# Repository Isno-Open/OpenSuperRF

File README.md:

# OpenSuperRF: the ISNO Super radio board, open

*(Version française : [README.fr.md](README.fr.md))*

**OpenSuperRF** is the open design of the **ISNO Super**: a sub-GHz radio board built around an
ESP32-S3, made to cleanly run open radio firmwares such as
[OpenProfalux](https://github.com/Isno-Open/OpenProfalux) (Profalux 868 MHz shutters in Home
Assistant, no gateway).

This is the **v1.0 (EVT)**, the version that was manufactured, assembled and measured. It is
published here as open hardware. The board sold as a pre-order is the **v1.1**, a refinement (see
[v1.0 open, v1.1 sold](#v10-open-v11-sold)).

> ⚠️ **Open points (v1.0 EVT).** This prototype has known open points, including a **J2 mikroBUS pinout that is destructive with a straight IDC cable**. Read [`KNOWN_ISSUES.md`](KNOWN_ISSUES.md) before building.

## What it is

- **ESP32-S3** over USB-C, powered by a 3.3 V LDO.
- **Two CC1101 radios**, **433 MHz and 868 MHz**, driven over SPI.
- On the v1.0, the two radios are combined onto a **single SMA** through an **LC diplexer**.
- **Qwiic** (I2C) and **mikroBUS** (2x8) for expansion.
- **BOOT** and **RESET** buttons, status LED.
- 4 layers, 67 x 55 mm. Board marking: `ISNO Super IoT HW REV 1.0`.

## Firmwares

The Super is not tied to one firmware, it is a board **for radio firmwares**. It notably runs:

- **[OpenProfalux](https://github.com/Isno-Open/OpenProfalux)** : Profalux 868 MHz shutters in Home
  Assistant, no gateway.
- **[OpenRFTest](https://github.com/Isno-Open/OpenRFTest)** : radio test firmware (TX/RX).

## RF measurements (v1.0, tinySA)

The v1.0 was measured: single, clean carriers, low noise floor, no spurious emissions over the
observed window.

## Schematic and pinout

mikroBUS (left column): AN 8, RST 40, CS 34, SCK 36, MISO 37, MOSI 35, 3.3 V, GND.
mikroBUS (right column): PWM 38, INT 39, RX 18, TX 17, SCL 13, SDA 12, 5 V, GND.
Qwiic: GND, 3.3 V, SDA 12, SCL 13.

The full schematic is in [`docs/isno-super-v1.0-schematic.pdf`](docs/isno-super-v1.0-schematic.pdf).

## Enclosure

A 3D-printable enclosure is provided in [`enclosures/`](enclosures/) (`boitier_super.stl`). The board
also fits DIN-rail and IP65 enclosures.

## Accessories

Open here as well (produced, unchanged since). KiCad sources in [`hardware/accessories/`](hardware/accessories/).

- **mikroBUS riser**: raises and offsets the mikroBUS socket.
- **mikroBUS adapter**.

## v1.0 open, v1.1 sold

To be clear, and honest:

- **v1.0** (here, open): the two radios combined onto a **single SMA** through an **LC diplexer**. This
  is the tested and measured version, published as open hardware to study, build and modify.
- **v1.1** (sold as a [pre-order](https://www.isno.fr/boutique/isno-super)): same radio chain
  (ESP32-S3 + dual CC1101), but the diplexer is removed in favour of **two dedicated antenna
  connectors** (one per band). It is the refined, ready-to-use and supported evolution.

DIY therefore stays fully possible and free; the v1.1 is the "ready and reliable" option for those who
would rather not build it.

## Repository contents

- `hardware/super/` : KiCad source of the Super **v1.0** (schematic + PCB).
- `hardware/accessories/` : KiCad source of the accessories (mikroBUS riser, adapter).
- `hardware/OpenProfalux.pretty/`, `hardware/lib/` : custom footprints and symbols needed to open the
  project in KiCad. The `.pretty` library keeps its historical name (the board started under the
  OpenProfalux project); it is just the footprint library.
- `fab/` : the manufactured EVT outputs (Gerbers, BOM, CPL, 3D render, EMC and thermal reports).
- `enclosures/` : 3D-printable enclosure.
- `docs/` : schematic PDF, BOM, production notes.
- `images/` : photos, RF measurements, renders.

## Licence

Hardware: **CERN-OHL-S v2** (see [`LICENSE`](LICENSE)). Associated firmwares: see their own repos.

## Links

- Ready-to-use board (v1.1): https://www.isno.fr/boutique/isno-super
- Project article (context, measurements, design choices): https://www.isno.fr/projets/isno-super
- Profalux shutters firmware: https://github.com/Isno-Open/OpenProfalux

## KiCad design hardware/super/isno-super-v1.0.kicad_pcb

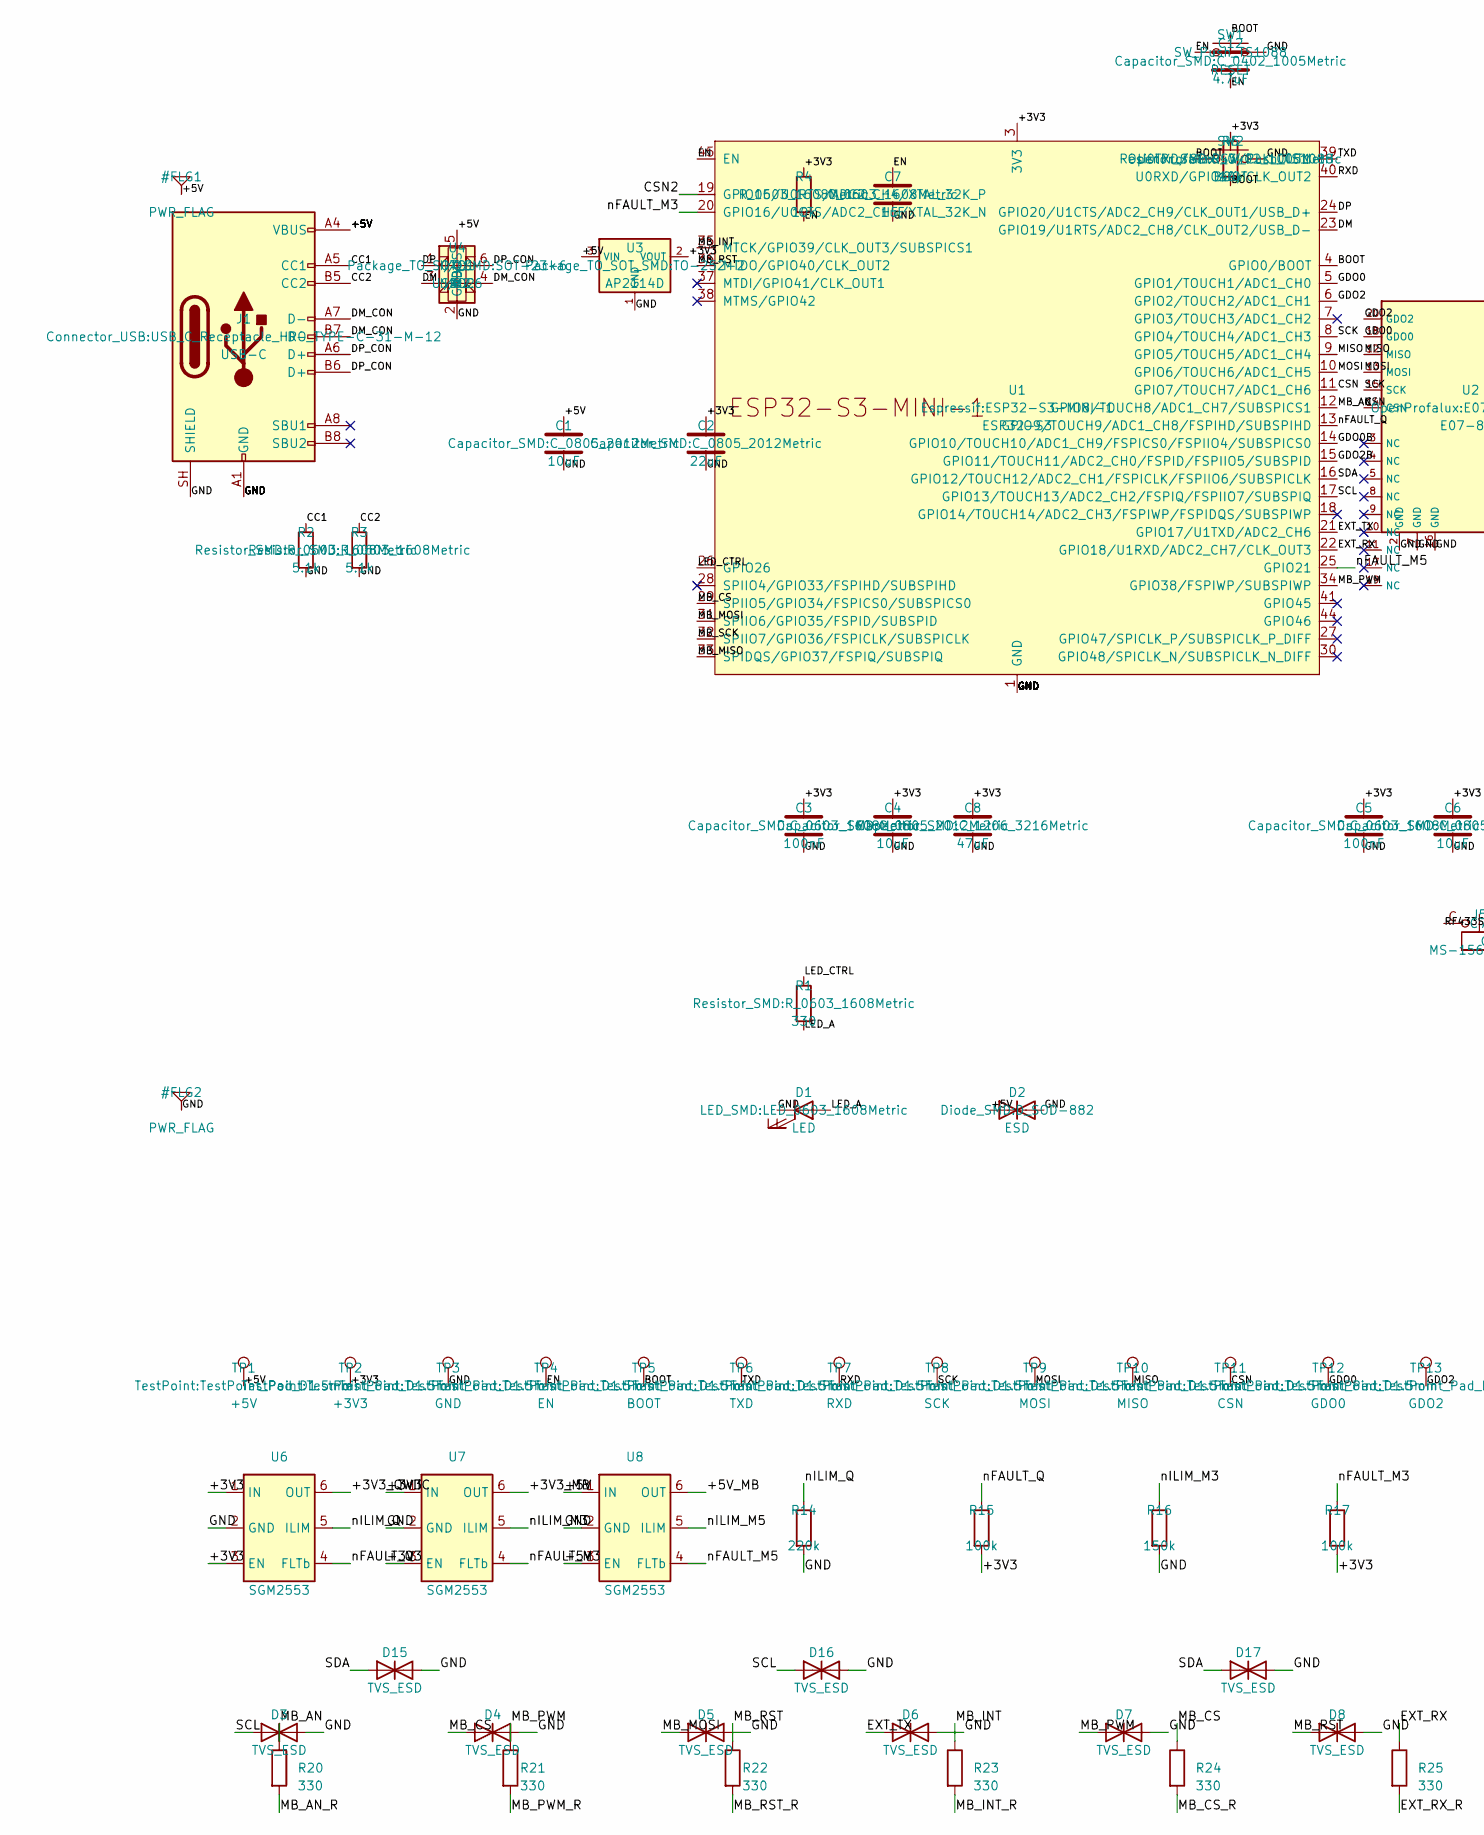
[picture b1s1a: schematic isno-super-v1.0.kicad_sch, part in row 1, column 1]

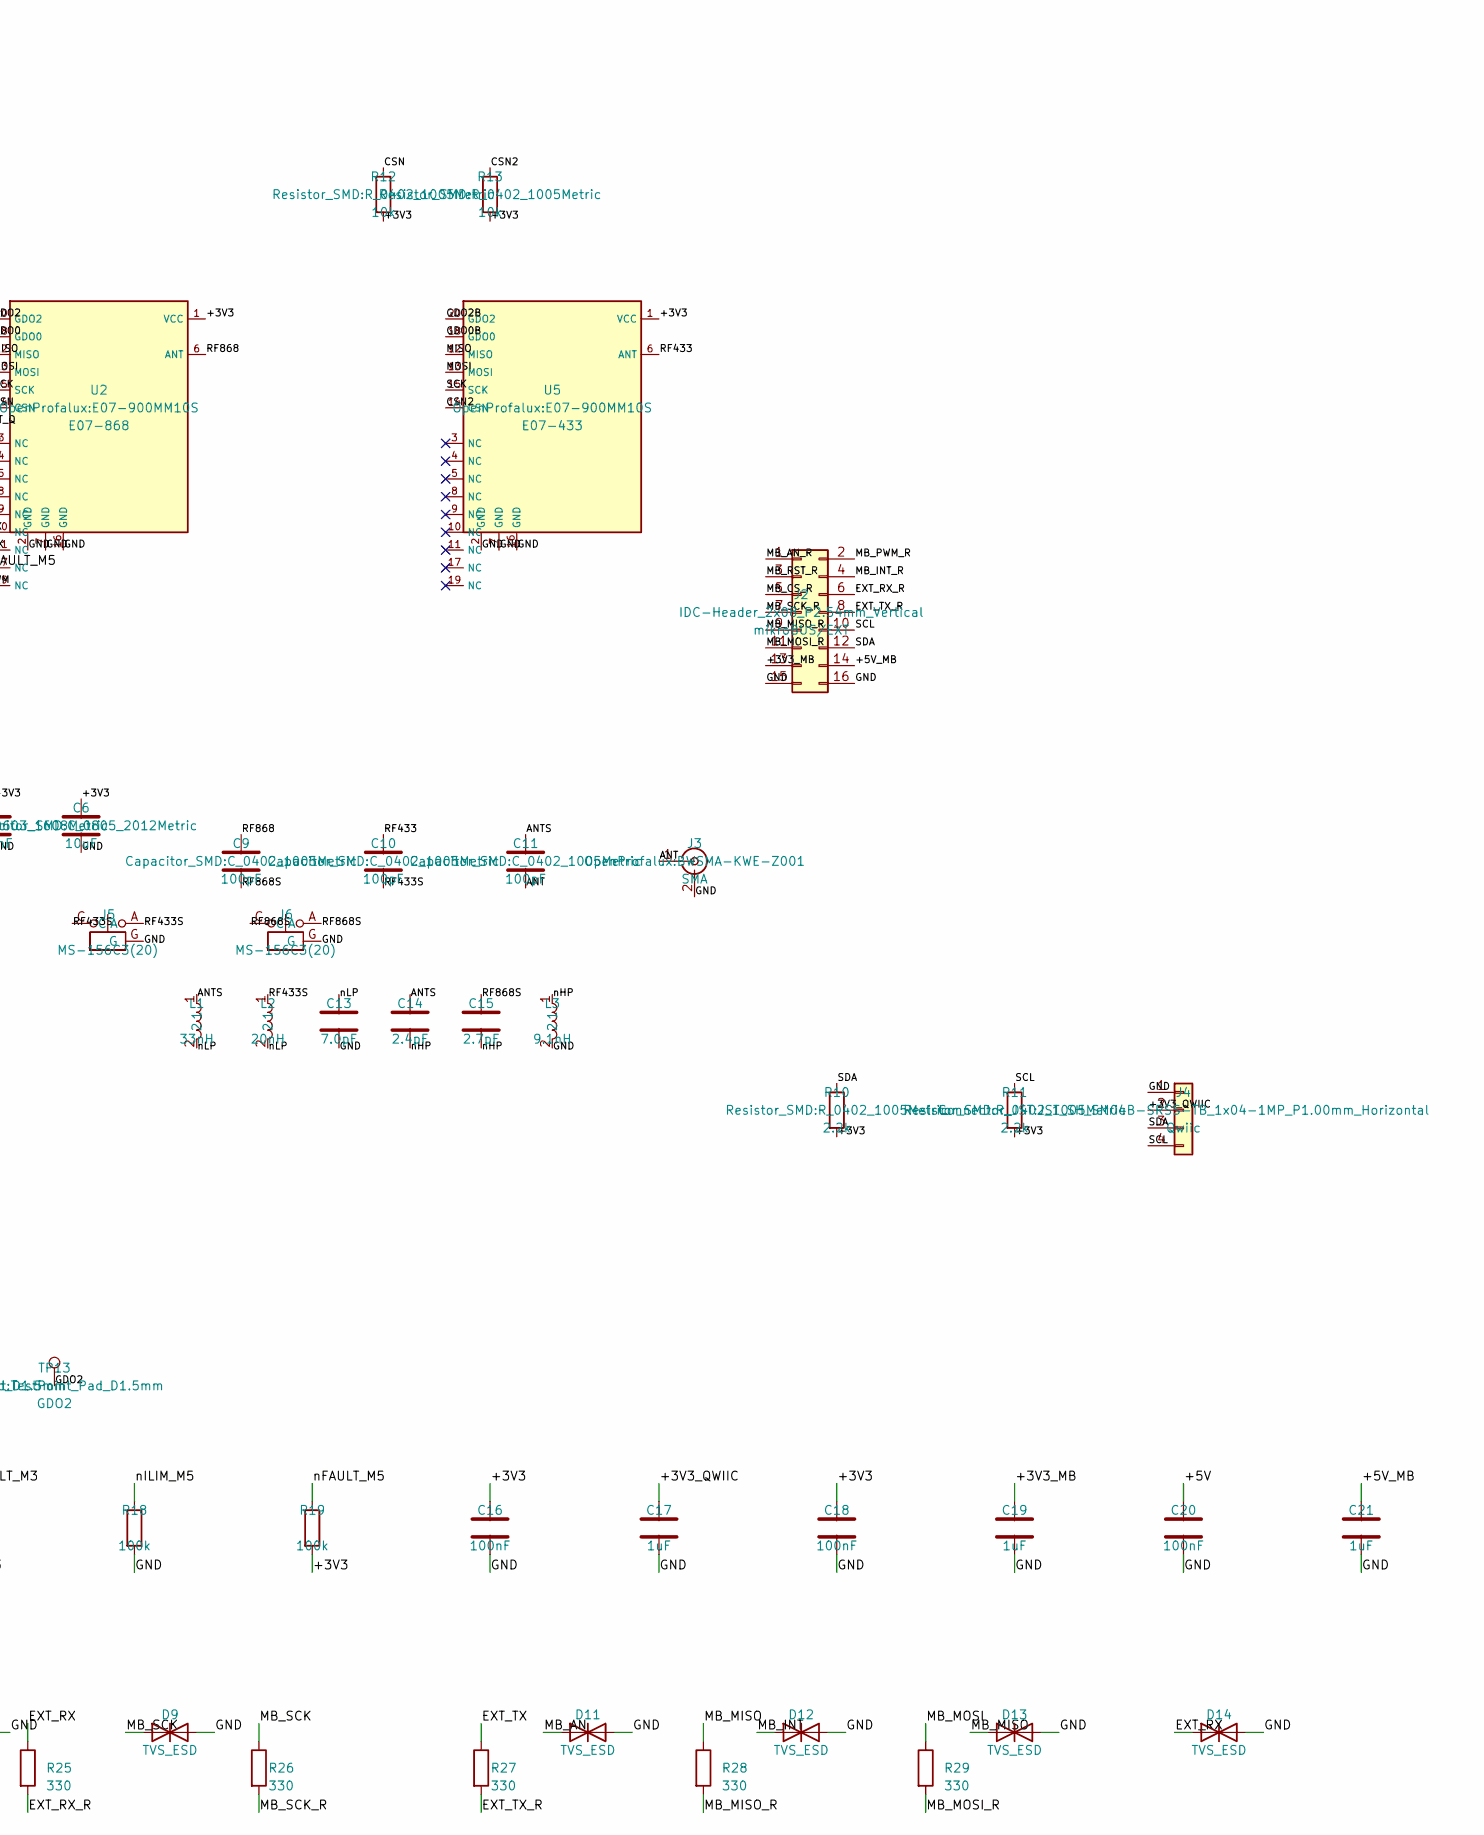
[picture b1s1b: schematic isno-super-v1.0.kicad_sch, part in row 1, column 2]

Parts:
C1, C4, C6: 10uF; C_0805_2012Metric
C2: 22uF; C_0805_2012Metric
C3, C5: 100nF; C_0603_1608Metric
C7: 1uF; C_0603_1608Metric
C8: 47uF; C_1206_3216Metric
C9, C10, C11: 100pF; C_0402_1005Metric
C12: 4.7uF; C_0402_1005Metric
C13: 7.0pF; C_0402_1005Metric
C14: 2.4pF; C_0402_1005Metric
C15: 2.7pF; C_0402_1005Metric
C16, C18, C20: 100nF; C_0402_1005Metric
C17, C19, C21: 1uF; C_0402_1005Metric
D1: LED; LED_0603_1608Metric
D2: ESD; D_SOD-882
D3, D4, D5, D6, D7, D8, D9, D11, D12, D13, D14, D15, D16, D17: TVS_ESD; Texas_DPY0002A_0.6x1mm_P0.65mm
J1: USB-C; USB_C_Receptacle_HRO_TYPE-C-31-M-12
J2: mikroBUS/EXT; IDC-Header_2x08_P2.54mm_Vertical
J3: SMA; BWSMA-KWE-Z001
J4: Qwiic; JST_SH_SM04B-SRSS-TB_1x04-1MP_P1.00mm_Horizontal
J5, J6: MS-156C3(20); CoaxialSwitch_Hirose_MS-156C3_Horizontal
L1: 33nH; L_0402_1005Metric
L2: 20nH; L_0402_1005Metric
L3: 9.1nH; L_0402_1005Metric
R1: 330; R_0603_1608Metric
R2, R3: 5.1k; R_0603_1608Metric
R4: 10k; R_0603_1608Metric
R5, R12, R13: 10k; R_0402_1005Metric
R10, R11: 2.2k; R_0402_1005Metric
R14: 220k; R_0402_1005Metric
R15, R17, R18, R19: 100k; R_0402_1005Metric
R16: 150k; R_0402_1005Metric
R20, R21, R22, R23, R24, R25, R26, R27, R28, R29: 330; R_0402_1005Metric
SW1: RESET; SW_Push_TS1088
SW2: BOOT; SW_Push_TS1088
TP1: +5V; TestPoint_Pad_D1.5mm
TP2: +3V3; TestPoint_Pad_D1.5mm
TP3: GND; TestPoint_Pad_D1.5mm
TP4: EN; TestPoint_Pad_D1.5mm
TP5: BOOT; TestPoint_Pad_D1.5mm
TP6: TXD; TestPoint_Pad_D1.5mm
TP7: RXD; TestPoint_Pad_D1.5mm
TP8: SCK; TestPoint_Pad_D1.5mm
TP9: MOSI; TestPoint_Pad_D1.5mm
TP10: MISO; TestPoint_Pad_D1.5mm
TP11: CSN; TestPoint_Pad_D1.5mm
TP12: GDO0; TestPoint_Pad_D1.5mm
TP13: GDO2; TestPoint_Pad_D1.5mm
U1: ESP32-S3; ESP32-S3-MINI-1
U2: E07-868; E07-900MM10S
U3: AP2114D; TO-252-2
U4: USBLC6; SOT-23-6
U5: E07-433; E07-900MM10S
U6, U7, U8: SGM2553; SOT-23-6

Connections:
+3V3: C2.1, C3.1, C4.1, C5.1, C6.1, C8.1, C16.1, C18.1, R4.1, R5.1, R10.2, R11.2, R12.2, R13.2, R15.2, R17.2, R19.2, TP2.1, U1.3 (3V3), U2.1 (VCC), U3.2 (VOUT), U5.1 (VCC), U6.1 (IN), U6.3 (EN), U7.1 (IN), U7.3 (EN)
+3V3_MB: C19.1, J2.13, U7.6 (OUT)
+3V3_QWIIC: C17.1, J4.2, U6.6 (OUT)
+5V: C1.1, C20.1, D2.1 (A1), J1.A4 (VBUS), J1.A9 (VBUS), J1.B4 (VBUS), J1.B9 (VBUS), TP1.1, U3.3 (VIN), U4.5 (VBUS), U8.1 (IN), U8.3 (EN)
+5V_MB: C21.1, J2.14, U8.6 (OUT)
ANT: C11.2, J3.1 (In)
ANTS: C11.1, C14.1, L1.1
BOOT: C12.1, R5.2, SW2.1, TP5.1, U1.4 (GPIO0/BOOT)
CC1: J1.A5 (CC1), R2.1
CC2: J1.B5 (CC2), R3.1
CSN: R12.1, TP11.1, U1.11 (GPIO7/TOUCH7/ADC1_CH6), U2.14 (CSN)
CSN2: R13.1, U1.19 (GPIO15/U0RTS/ADC2_CH4/XTAL_32K_P), U5.14 (CSN)
DM: U1.23 (GPIO19/U1RTS/ADC2_CH8/CLK_OUT2/USB_D-), U4.3 (I/O2)
DM_CON: J1.A7 (D-), J1.B7 (D-), U4.4 (I/O2)
DP: U1.24 (GPIO20/U1CTS/ADC2_CH9/CLK_OUT1/USB_D+), U4.1 (I/O1)
DP_CON: J1.A6 (D+), J1.B6 (D+), U4.6 (I/O1)
EN: C7.1, C12.2, R4.2, SW1.1, TP4.1, U1.45 (EN)
EXT_RX: D14.1 (A1), R25.1, U1.22 (GPIO18/U1RXD/ADC2_CH7/CLK_OUT3)
EXT_RX_R: J2.6, R25.2
EXT_TX: D6.1 (A1), R27.1, U1.21 (GPIO17/U1TXD/ADC2_CH6)
EXT_TX_R: J2.8, R27.2
GDO0: TP12.1, U1.5 (GPIO1/TOUCH1/ADC1_CH0), U2.18 (GDO0)
GDO0B: U1.14 (GPIO10/TOUCH10/ADC1_CH9/FSPICS0/FSPIIO4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), U5.18 (GDO0)
GDO2: TP13.1, U1.6 (GPIO2/TOUCH2/ADC1_CH1), U2.20 (GDO2)
GDO2B: U1.15 (GPIO11/TOUCH11/ADC2_CH0/FSPID/FSPIIO5/S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), U5.20 (GDO2)
GND: C1.2, C2.2, C3.2, C4.2, C5.2, C6.2, C7.2, C8.2, C13.2, C16.2, C17.2, C18.2, C19.2, C20.2, C21.2, D1.1 (K), D2.2 (A2), D3.2 (A2), D4.2 (A2), D5.2 (A2), D6.2 (A2), D7.2 (A2), D8.2 (A2), D9.2 (A2), D11.2 (A2), D12.2 (A2), D13.2 (A2), D14.2 (A2), D15.2 (A2), D16.2 (A2), D17.2 (A2), J1.A1 (GND), J1.A12 (GND), J1.B1 (GND), J1.B12 (GND), J1.SH (SHIELD), J2.15, J2.16, J3.2 (Ext), J4.1, J4.MP, J5.G, J5.G1, J5.G2, J6.G, J6.G1, J6.G2, L3.2, R2.2, R3.2, R14.2, R16.2, R18.2, SW1.2, SW2.2, TP3.1, U1.1 (GND), U1.2 (GND), U1.42 (GND), U1.43 (GND), U1.46 (GND), U1.47 (GND), U1.48 (GND), U1.49 (GND), U1.50 (GND), U1.51 (GND), U1.52 (GND), U1.53 (GND), U1.54 (GND), U1.55 (GND), U1.56 (GND), U1.57 (GND), U1.58 (GND), U1.59 (GND), U1.60 (GND), U1.61 (GND), U1.62 (GND), U1.63 (GND), U1.64 (GND), U1.65 (GND), U2.2 (GND), U2.7 (GND), U2.16 (GND), U3.1 (GND), U4.2 (GND), U5.2 (GND), U5.7 (GND), U5.16 (GND), U6.2 (GND), U7.2 (GND), U8.2 (GND)
LED_A: D1.2 (A), R1.2
LED_CTRL: R1.1, U1.26 (GPIO26)
MB_AN: D11.1 (A1), R20.1, U1.12 (GPIO8/TOUCH8/ADC1_CH7/SUBSPICS1)
MB_AN_R: J2.1, R20.2
MB_CS: D4.1 (A1), R24.1, U1.29 (SPIIO5/GPIO34/FSPICS0/SUBSPICS0)
MB_CS_R: J2.5, R24.2
MB_INT: D12.1 (A1), R23.1, U1.35 (MTCK/GPIO39/CLK_OUT3/SUBSPICS1)
MB_INT_R: J2.4, R23.2
MB_MISO: D13.1 (A1), R28.1, U1.33 (SPIDQS/GPIO37/FSPIQ/SUBSPIQ)
MB_MISO_R: J2.9, R28.2
MB_MOSI: D5.1 (A1), R29.1, U1.31 (SPIIO6/GPIO35/FSPID/SUBSPID)
MB_MOSI_R: J2.11, R29.2
MB_PWM: D7.1 (A1), R21.1, U1.34 (GPIO38/FSPIWP/SUBSPIWP)
MB_PWM_R: J2.2, R21.2
MB_RST: D8.1 (A1), R22.1, U1.36 (MTDO/GPIO40/CLK_OUT2)
MB_RST_R: J2.3, R22.2
MB_SCK: D9.1 (A1), R26.1, U1.32 (SPIIO7/GPIO36/FSPICLK/SUBSPICLK)
MB_SCK_R: J2.7, R26.2
MISO: TP10.1, U1.9 (GPIO5/TOUCH5/ADC1_CH4), U2.12 (MISO), U5.12 (MISO)
MOSI: TP9.1, U1.10 (GPIO6/TOUCH6/ADC1_CH5), U2.13 (MOSI), U5.13 (MOSI)
RF433: C10.1, U5.6 (ANT)
RF433S: C10.2, J5.1, J5.A, J5.C, L2.1
RF868: C9.1, U2.6 (ANT)
RF868S: C9.2, C15.1, J6.1, J6.A, J6.C
RXD: TP7.1, U1.40 (U0RXD/GPIO44/CLK_OUT2)
SCK: TP8.1, U1.8 (GPIO4/TOUCH4/ADC1_CH3), U2.15 (SCK), U5.15 (SCK)
SCL: D3.1 (A1), D16.1 (A1), J2.10, J4.4, R11.1, U1.17 (GPIO13/TOUCH13/ADC2_CH2/FSPIQ/FSPIIO7/S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)
SDA: D15.1 (A1), D17.1 (A1), J2.12, J4.3, R10.1, U1.16 (GPIO12/TOUCH12/ADC2_CH1/FSPICLK/FSPIIO6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)
TXD: TP6.1, U1.39 (U0TXD/GPIO43/CLK_OUT1)
nFAULT_M3: R17.1, U1.20 (GPIO16/U0CTS/ADC2_CH5/XTAL_32K_N), U7.4 (FLTb)
nFAULT_M5: R19.1, U1.25 (GPIO21), U8.4 (FLTb)
nFAULT_Q: R15.1, U1.13 (GPIO9/TOUCH9/ADC1_CH8/FSPIHD/SUBSPIHD), U6.4 (FLTb)
nHP: C14.2, C15.2, L3.1
nILIM_M3: R16.1, U7.5 (ILIM)
nILIM_M5: R18.1, U8.5 (ILIM)
nILIM_Q: R14.1, U6.5 (ILIM)
nLP: C13.1, L1.2, L2.2

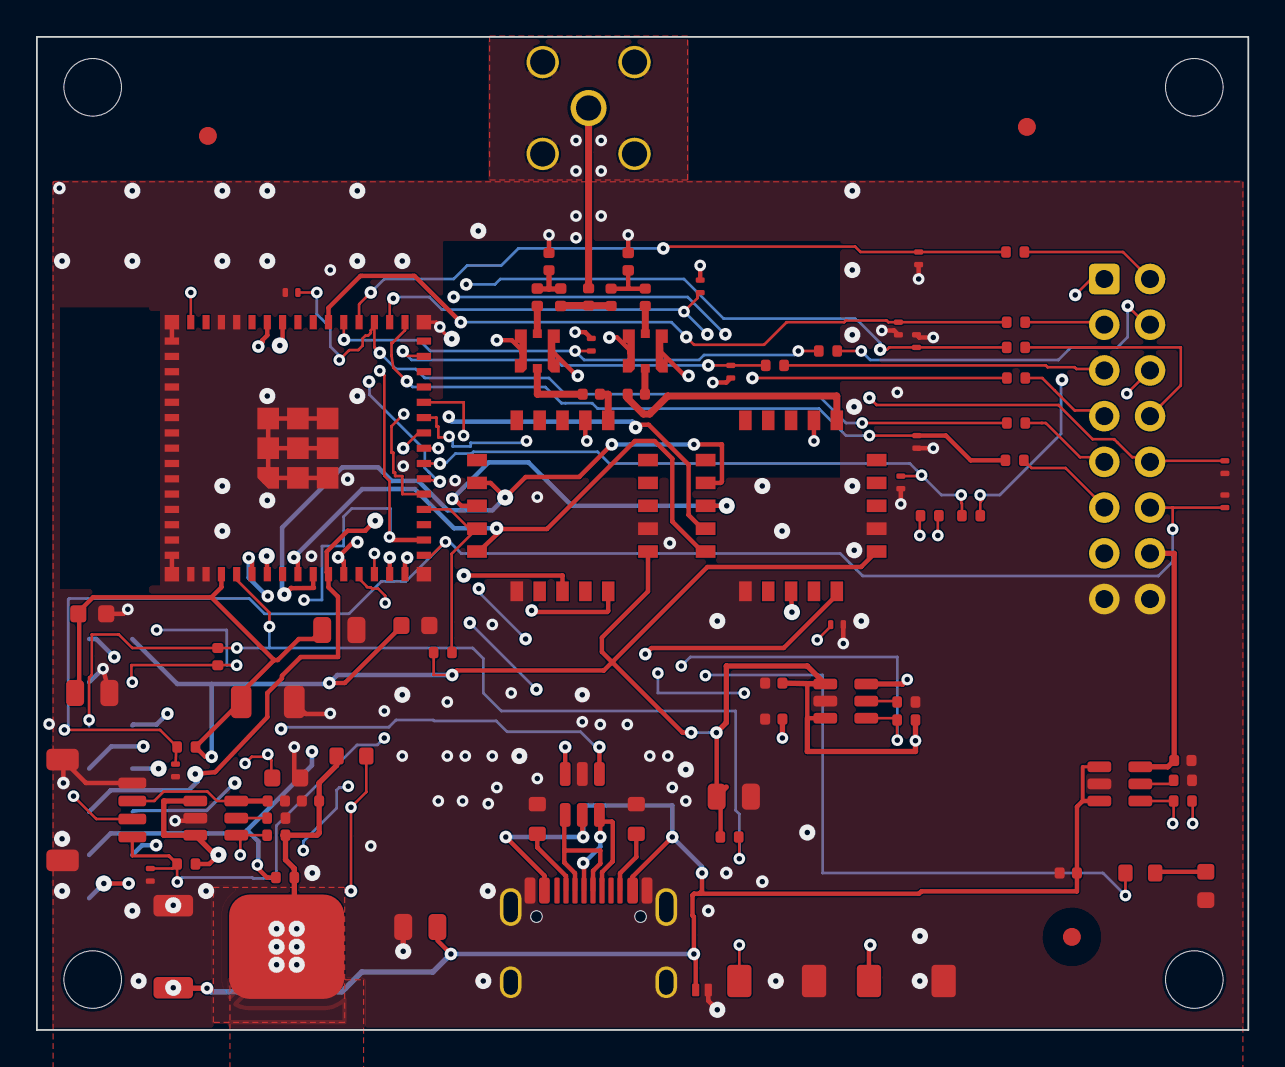
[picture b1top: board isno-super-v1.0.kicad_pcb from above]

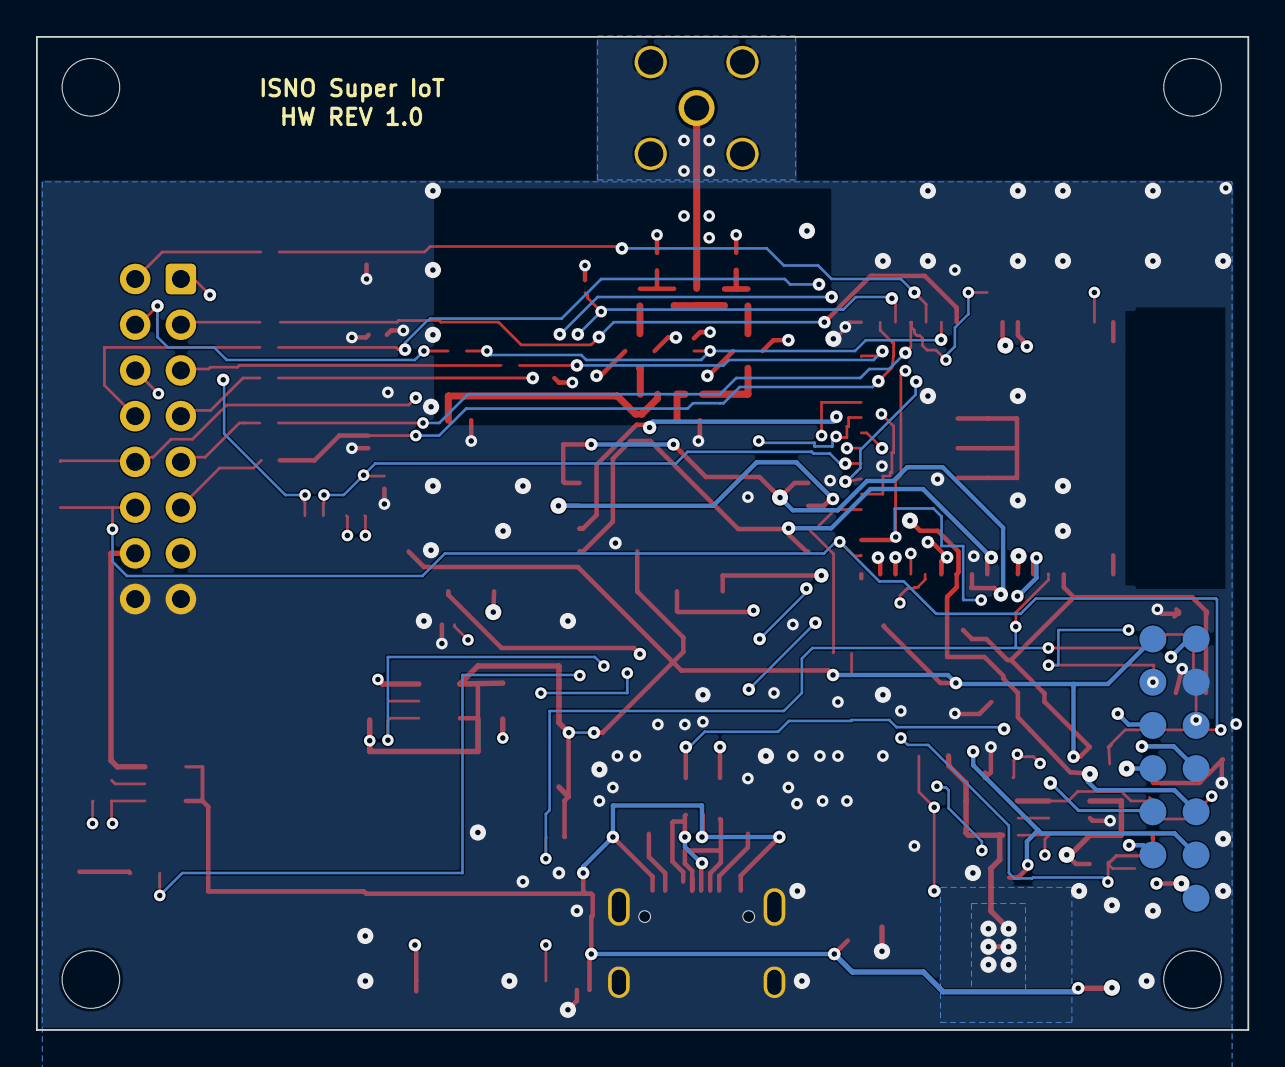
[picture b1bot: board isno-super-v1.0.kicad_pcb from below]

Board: 4 copper layers, 67.3 x 55.2 mm, 101 parts (13 on the bottom side), 63 nets.

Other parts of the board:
FID1, FID2, FID3: Fiducial
H1, H2, H3, H4: M3; MountingHole_3.2mm_M3

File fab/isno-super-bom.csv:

Comment,Designator,Footprint,LCSC Part #
10uF,"C1,C4,C6",C_0805_2012Metric,C15850
22uF,C2,C_0805_2012Metric,C45783
100nF,"C3,C5",C_0603_1608Metric,C14663
1uF,C7,C_0603_1608Metric,C29936
47uF,C8,C_1206_3216Metric,C96123
100pF,"C9,C10,C11",C_0402_1005Metric,C1546
4.7uF,C12,C_0402_1005Metric,C23733
7.0pF,C13,C_0402_1005Metric,C161333
2.4pF,C14,C_0402_1005Metric,C88889
2.7pF,C15,C_0402_1005Metric,C76904
100nF,"C16,C18,C20",C_0402_1005Metric,C1525
1uF,"C17,C19,C21",C_0402_1005Metric,C52923
LED,D1,LED_0603_1608Metric,C2290
ESD,D2,D_SOD-882,C85402
TVS_ESD,"D3,D4,D5,D6,D7,D8,D9,D11,D12,D13,D14,D15,D16,D17",Texas_DPY0002A_0.6x1mm_P0.65mm,C48260
USB-C,J1,USB_C_Receptacle_HRO_TYPE-C-31-M-12,C165948
mikroBUS IDC box 2x8,J2,IDC-Header_2x08_P2.54mm_Vertical,C492443
SMA RA THT 50R,J3,BWSMA-KWE-Z001,C496551
Qwiic,J4,JST_SH_SM04B-SRSS-TB_1x04-1MP_P1.00mm_Horizontal,C160404
MS-156C3(20),"J5,J6",CoaxialSwitch_Hirose_MS-156C3_Horizontal,C3173236
33nH,L1,L_0402_1005Metric,C113114
20nH,L2,L_0402_1005Metric,C2043868
9.1nH,L3,L_0402_1005Metric,C113122
330,R1,R_0603_1608Metric,C23138
5.1k,"R2,R3",R_0603_1608Metric,C23186
10k,R4,R_0603_1608Metric,C98220
10k,"R5,R12,R13",R_0402_1005Metric,C25744
2.2k,"R10,R11",R_0402_1005Metric,C25879
220k,R14,R_0402_1005Metric,C25767
100k,"R15,R17,R18,R19",R_0402_1005Metric,C25741
150k,R16,R_0402_1005Metric,C25755
330,"R20,R21,R22,R23,R24,R25,R26,R27,R28,R29",R_0402_1005Metric,C25104
RESET,SW1,SW_Push_TS1088,C720477
SW push,SW2,SW_Push_TS1088,C720477
ESP32-S3,U1,ESP32-S3-MINI-1,C2913206
E07-868,U2,E07-900MM10S,C5844212
AP2114D,U3,TO-252-2,C460311
USBLC6,U4,SOT-23-6,C7519
E07-433,U5,E07-900MM10S,C5844213
SGM2553,"U6,U7,U8",SOT-23-6,C699882

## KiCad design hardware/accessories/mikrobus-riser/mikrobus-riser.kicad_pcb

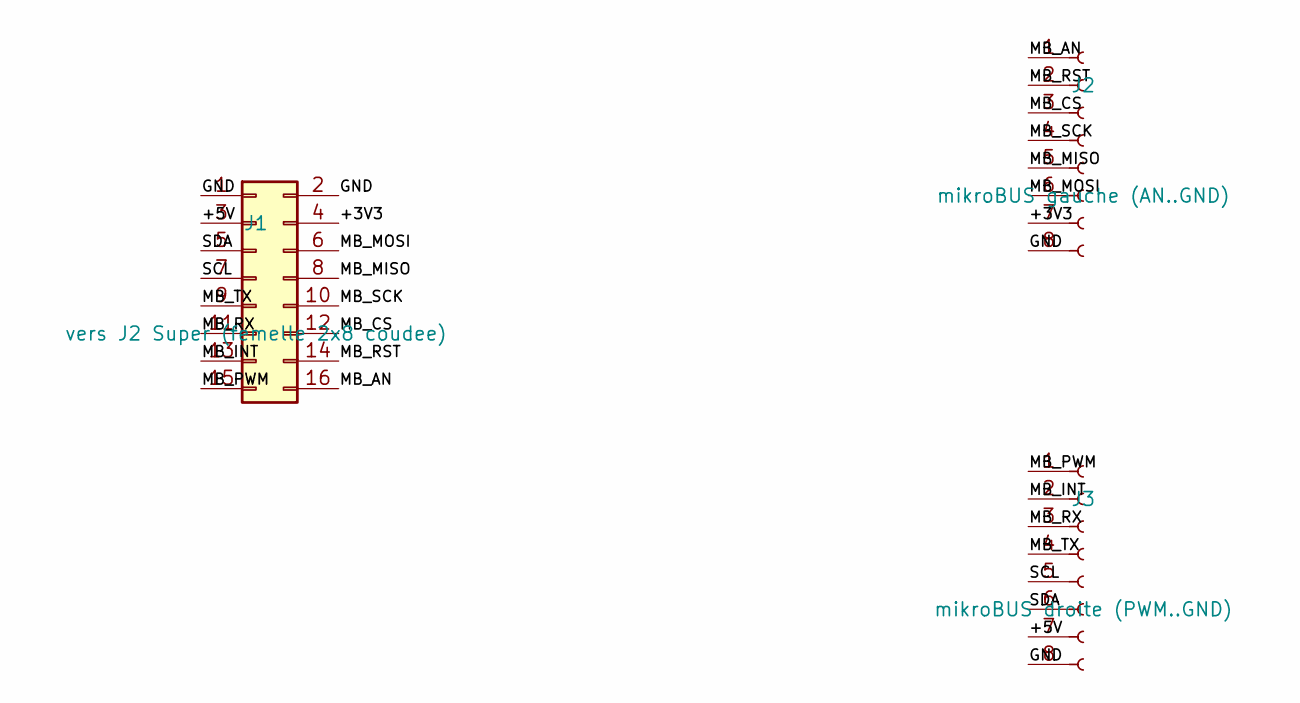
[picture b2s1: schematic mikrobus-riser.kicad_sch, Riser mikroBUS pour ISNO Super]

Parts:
J1: vers J2 Super (femelle 2x8 coudee); PinSocket_2x08_P2.54mm_Horizontal; LCSC C7509538
J2: mikroBUS gauche (AN..GND); PinSocket_1x08_P2.54mm_Vertical; LCSC C27438
J3: mikroBUS droite (PWM..GND); PinSocket_1x08_P2.54mm_Vertical; LCSC C27438

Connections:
+3V3: J1.4, J2.7
+5V: J1.3, J3.7
GND: J1.1, J1.2, J2.8, J3.8
MB_AN: J1.16, J2.1
MB_CS: J1.12, J2.3
MB_INT: J1.13, J3.2
MB_MISO: J1.8, J2.5
MB_MOSI: J1.6, J2.6
MB_PWM: J1.15, J3.1
MB_RST: J1.14, J2.2
MB_RX: J1.11, J3.3
MB_SCK: J1.10, J2.4
MB_TX: J1.9, J3.4
SCL: J1.7, J3.5
SDA: J1.5, J3.6

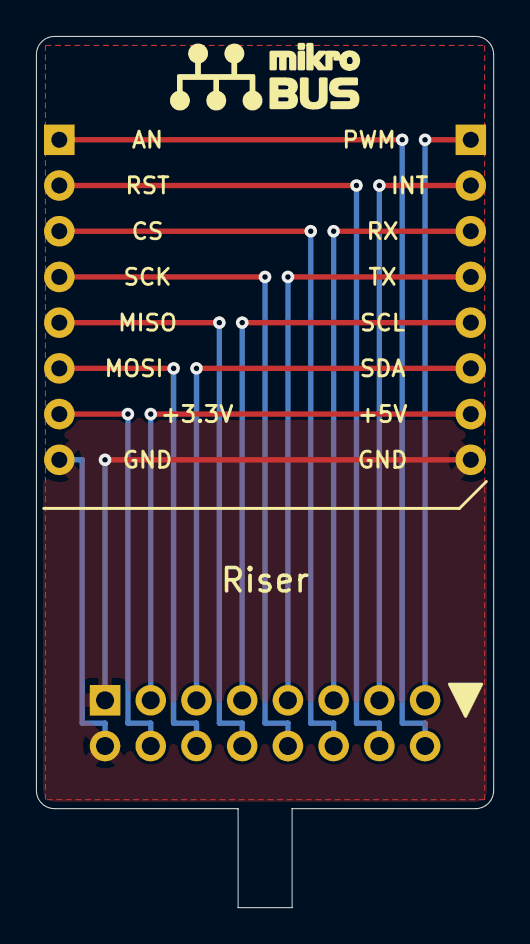
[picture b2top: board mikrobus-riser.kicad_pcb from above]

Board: 2 copper layers, 25.4 x 48.4 mm, 3 parts (0 on the bottom side), 15 nets.
